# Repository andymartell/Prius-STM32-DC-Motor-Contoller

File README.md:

# Prius-STM32-DC-Motor-Contoller

18/10/20  Updated the following:

- corrected tracking error around MG1 and MG2 current sensors.  J7 footprint updated (J1 left unchanged as tracking layout is currently ok).
- updated file names to remove spaces
- removed SG3204 and TX4313 -5V charge pumps and added LM2776 in their place in line with Jack Bauers latest updates

17/10/20  Initial release of files for manufacture.  
There are issues with these files, so use at your own risk.  
An updated version will follow once initial testing is complete!

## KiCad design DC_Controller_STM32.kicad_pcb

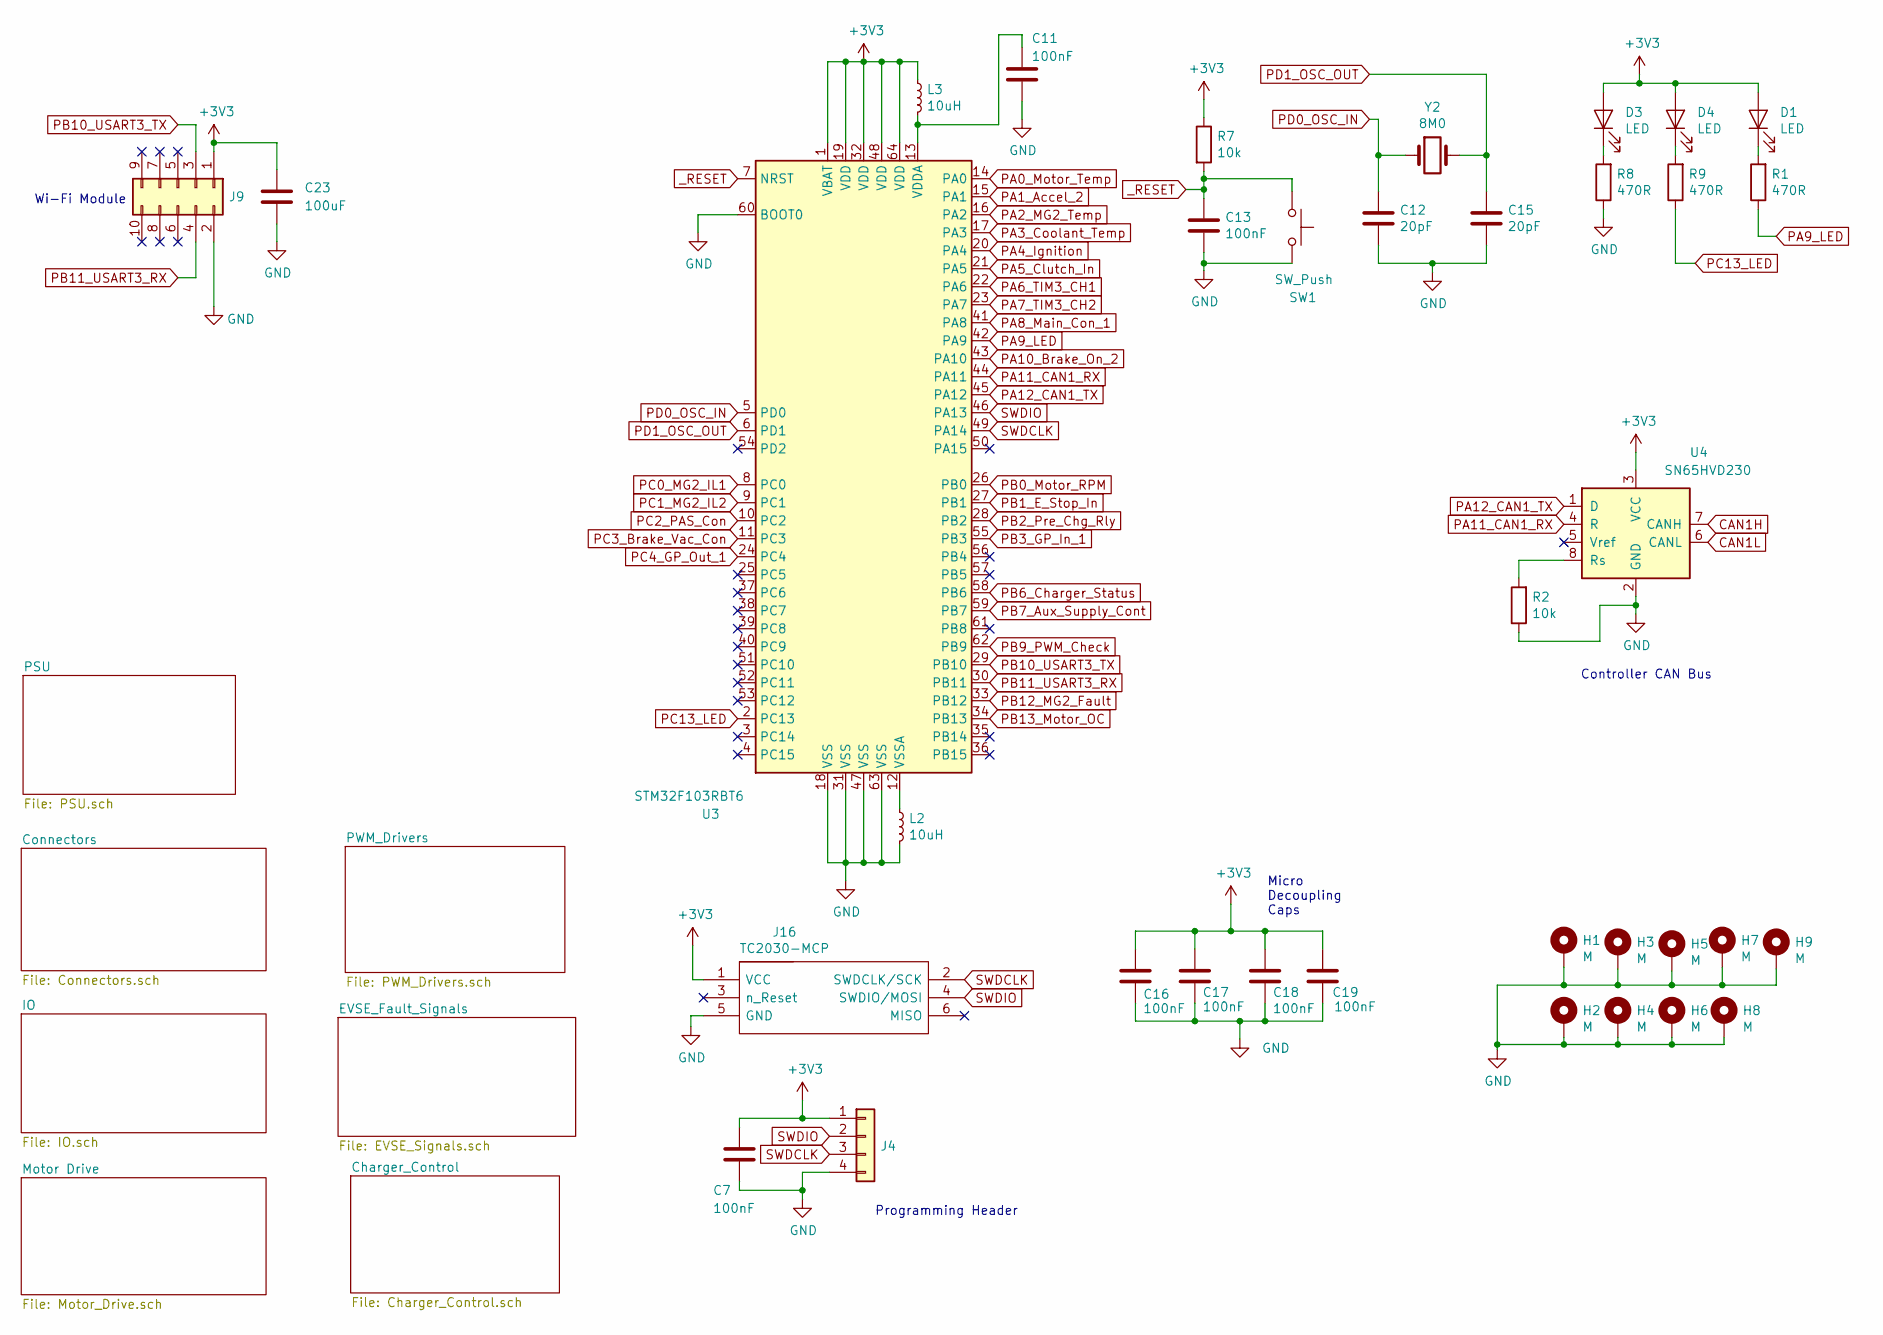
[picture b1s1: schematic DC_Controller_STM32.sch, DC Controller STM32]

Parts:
C7, C11, C13, C16, C17, C18, C19: 100nF; C_0603_1608Metric
C12, C15: 20pF; C_0603_1608Metric
C23: 100uF; CP_EIA-3528-21_Kemet-B
D1, D3, D4: LED; LED_0805_2012Metric
H1, H2, H3, H4, H5, H6, H7, H8, H9: M; MountingHole_3.2mm_M3_Pad
J4: Conn_01x04; PinHeader_1x04_P2.54mm_Vertical
J9: Conn_02x05_Odd_Even; PinHeader_2x05_P2.54mm_Horizontal
J16: TC2030-MCP; TC2030MCP; Manufacturer_Part_Number TC2030-MCP
L2, L3: 10uH; L_0805_2012Metric
R1, R8, R9: 470R; R_0603_1608Metric
R2, R7: 10k; R_0603_1608Metric
SW1: SW_Push; Panasonic_EVQPUK_EVQPUB
U3: STM32F103RBT6; LQFP-64_10x10mm_P0.5mm
U4: SN65HVD230; SOIC-8_3.9x4.9mm_P1.27mm
Y2: 8M0; Crystal_SMD_5032-2Pin_5.0x3.2mm

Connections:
+3V3: C7.1, C16.1, C17.1, C18.1, C19.1, C23.1, D1.2 (A), D3.2 (A), D4.2 (A), J4.1, J9.1, J16.1 (VCC), L3.1, R7.1, U3.1 (VBAT), U3.19 (VDD), U3.32 (VDD), U3.48 (VDD), U3.64 (VDD), U4.3 (VCC); also elsewhere on the board
CAN1H: U4.7 (CANH); also elsewhere on the board
CAN1L: U4.6 (CANL); also elsewhere on the board
GND: C7.2, C11.2, C12.2, C13.2, C15.2, C16.2, C17.2, C18.2, C19.2, C23.2, H1.1, H2.1, H3.1, H4.1, H5.1, H6.1, H7.1, H8.1, H9.1, J4.4, J9.2, J16.5 (GND), L2.2, R2.1, R8.1, SW1.2, U3.18 (VSS), U3.31 (VSS), U3.47 (VSS), U3.60 (BOOT0), U3.63 (VSS), U4.2 (GND); also elsewhere on the board
unnamed: C11.1, L3.2, U3.13 (VDDA)
unnamed: D1.1 (K), R1.2
unnamed: D3.1 (K), R8.2
unnamed: D4.1 (K), R9.2
unnamed: L2.1, U3.12 (VSSA)
unnamed: R2.2, U4.8 (Rs)
PA0_Motor_Temp: U3.14 (PA0); also elsewhere on the board
PA1_Accel_2: U3.15 (PA1); also elsewhere on the board
PA2_MG2_Temp: U3.16 (PA2); also elsewhere on the board
PA3_Coolant_Temp: U3.17 (PA3); also elsewhere on the board
PA4_Ignition: U3.20 (PA4); also elsewhere on the board
PA5_Clutch_In: U3.21 (PA5); also elsewhere on the board
PA6_TIM3_CH1: U3.22 (PA6); also elsewhere on the board
PA7_TIM3_CH2: U3.23 (PA7); also elsewhere on the board
PA8_Main_Con_1: U3.41 (PA8); also elsewhere on the board
PA9_LED: R1.1, U3.42 (PA9)
PA10_Brake_On_2: U3.43 (PA10); also elsewhere on the board
PA11_CAN1_RX: U3.44 (PA11), U4.4 (R)
PA12_CAN1_TX: U3.45 (PA12), U4.1 (D)
PB0_Motor_RPM: U3.26 (PB0); also elsewhere on the board
PB1_E_Stop_In: U3.27 (PB1); also elsewhere on the board
PB2_Pre_Chg_Rly: U3.28 (PB2); also elsewhere on the board
PB3_GP_In_1: U3.55 (PB3); also elsewhere on the board
PB6_Charger_Status: U3.58 (PB6); also elsewhere on the board
PB7_Aux_Supply_Cont: U3.59 (PB7); also elsewhere on the board
PB9_PWM_Check: U3.62 (PB9); also elsewhere on the board
PB10_USART3_TX: J9.3, U3.29 (PB10)
PB11_USART3_RX: J9.4, U3.30 (PB11)
PB12_MG2_Fault: U3.33 (PB12); also elsewhere on the board
PB13_Motor_OC: U3.34 (PB13); also elsewhere on the board
PC0_MG2_IL1: U3.8 (PC0); also elsewhere on the board
PC1_MG2_IL2: U3.9 (PC1); also elsewhere on the board
PC2_PAS_Con: U3.10 (PC2); also elsewhere on the board
PC3_Brake_Vac_Con: U3.11 (PC3); also elsewhere on the board
PC4_GP_Out_1: U3.24 (PC4); also elsewhere on the board
PC13_LED: R9.1, U3.2 (PC13)
PD0_OSC_IN: C12.1, U3.5 (PD0), Y2.1
PD1_OSC_OUT: C15.1, U3.6 (PD1), Y2.2
SWDCLK: J4.3, J16.2 (SWDCLK/SCK), U3.49 (PA14)
SWDIO: J4.2, J16.4 (SWDIO/MOSI), U3.46 (PA13)
_RESET: C13.1, R7.2, SW1.1, U3.7 (NRST)

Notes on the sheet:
Programming Header
Wi-Fi Module
Micro Decoupling Caps
Controller CAN Bus

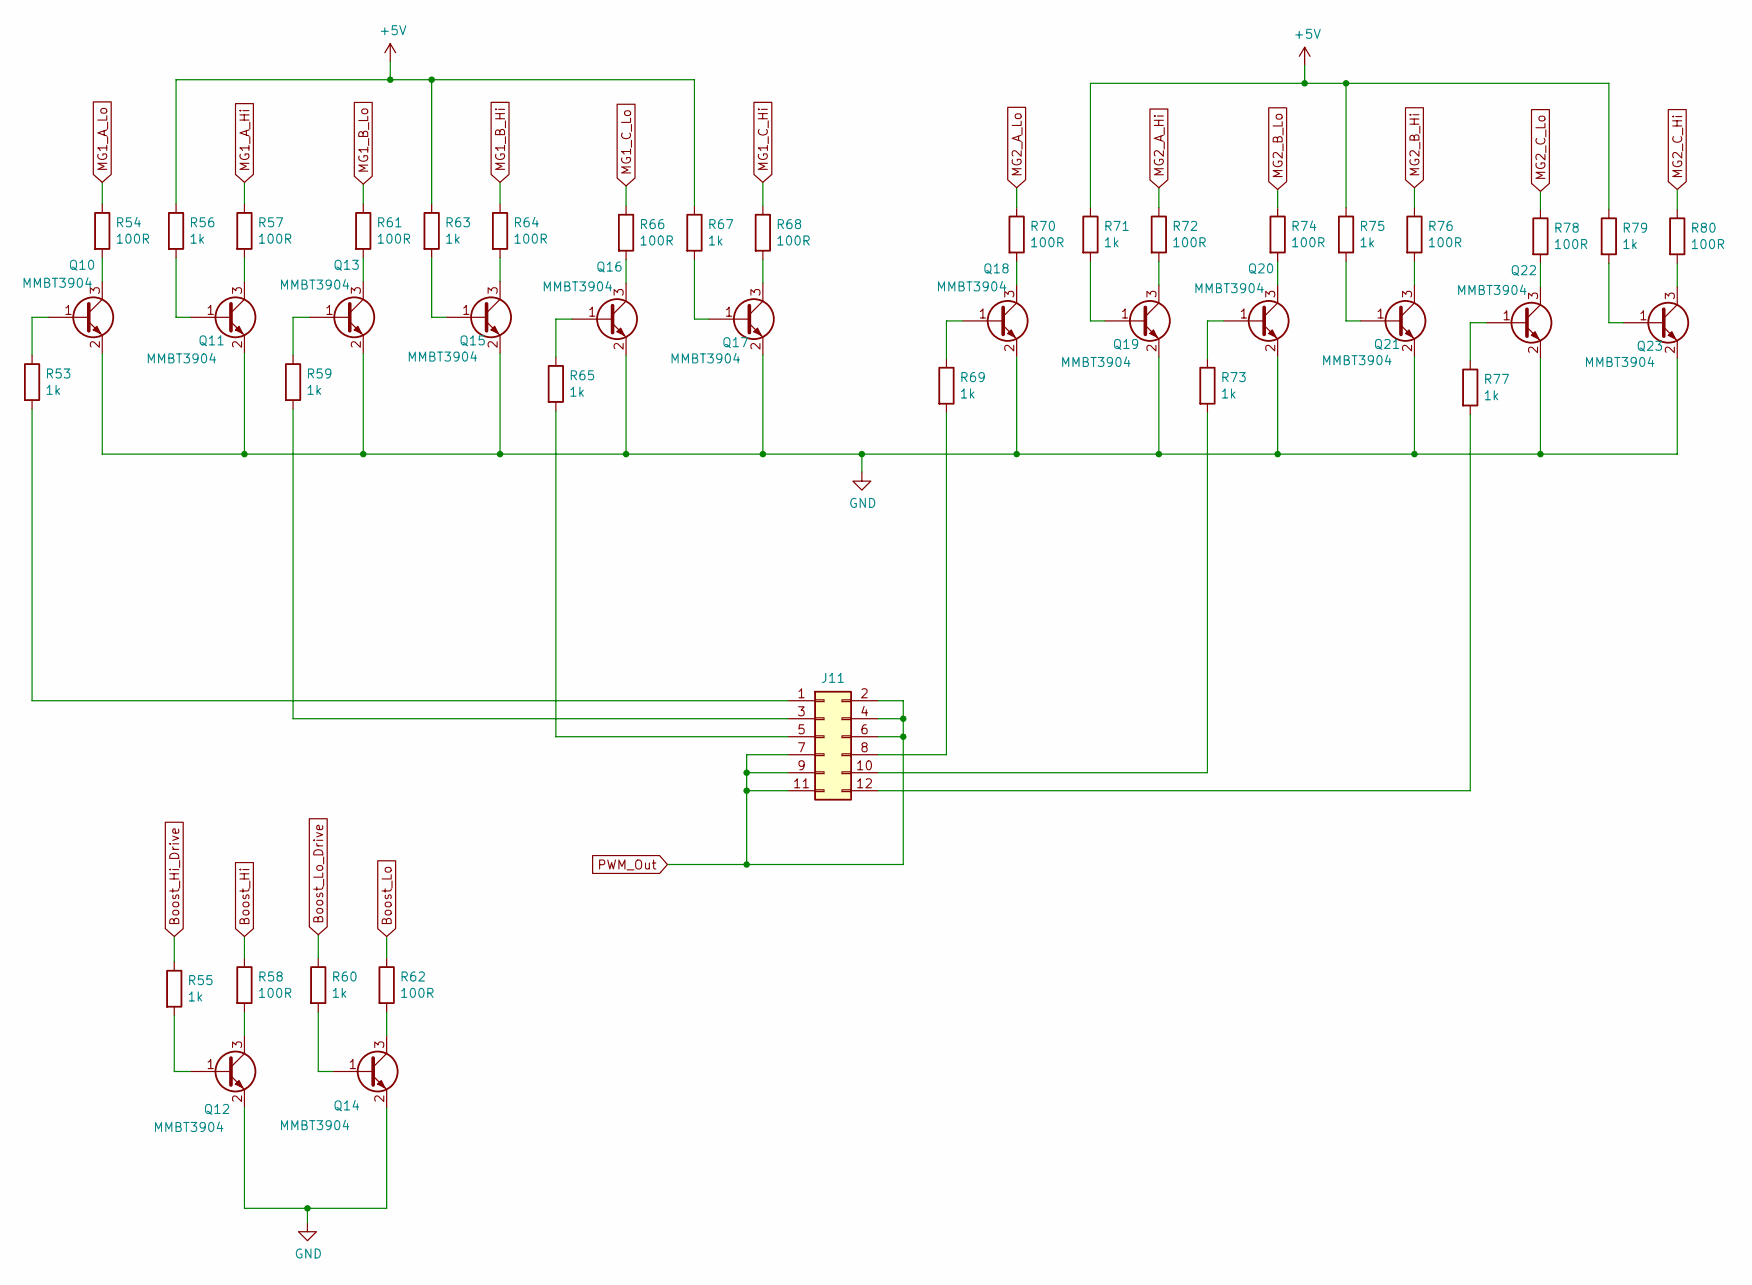
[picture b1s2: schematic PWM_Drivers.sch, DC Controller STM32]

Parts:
J11: Conn_02x06_Odd_Even; PinHeader_2x06_P2.54mm_Vertical
Q10, Q11, Q12, Q13, Q14, Q15, Q16, Q17, Q18, Q19, Q20, Q21, Q22, Q23: MMBT3904; SOT-23
R53, R55, R56, R59, R60, R63, R65, R67, R69, R71, R73, R75, R77, R79: 1k; R_0603_1608Metric
R54, R57, R58, R61, R62, R64, R66, R68, R70, R72, R74, R76, R78, R80: 100R; R_0603_1608Metric

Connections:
+5V: R56.1, R63.1, R67.1, R71.1, R75.1, R79.1; also elsewhere on the board
Boost_Hi: R58.1; also elsewhere on the board
Boost_Hi_Drive: R55.1; also elsewhere on the board
Boost_Lo: R62.1; also elsewhere on the board
Boost_Lo_Drive: R60.1; also elsewhere on the board
GND: Q10.2 (E), Q11.2 (E), Q12.2 (E), Q13.2 (E), Q14.2 (E), Q15.2 (E), Q16.2 (E), Q17.2 (E), Q18.2 (E), Q19.2 (E), Q20.2 (E), Q21.2 (E), Q22.2 (E), Q23.2 (E); also elsewhere on the board
MG1_A_Hi: R57.1; also elsewhere on the board
MG1_A_Lo: R54.1; also elsewhere on the board
MG1_B_Hi: R64.1; also elsewhere on the board
MG1_B_Lo: R61.1; also elsewhere on the board
MG1_C_Hi: R68.1; also elsewhere on the board
MG1_C_Lo: R66.1; also elsewhere on the board
MG2_A_Hi: R72.1; also elsewhere on the board
MG2_A_Lo: R70.1; also elsewhere on the board
MG2_B_Hi: R76.1; also elsewhere on the board
MG2_B_Lo: R74.1; also elsewhere on the board
MG2_C_Hi: R80.1; also elsewhere on the board
MG2_C_Lo: R78.1; also elsewhere on the board
unnamed: J11.1, R53.2
unnamed: J11.3, R59.2
unnamed: J11.5, R65.2
unnamed: J11.8, R69.2
unnamed: J11.10, R73.2
unnamed: J11.12, R77.2
unnamed: Q10.1 (B), R53.1
unnamed: Q10.3 (C), R54.2
unnamed: Q11.1 (B), R56.2
unnamed: Q11.3 (C), R57.2
unnamed: Q12.1 (B), R55.2
unnamed: Q12.3 (C), R58.2
unnamed: Q13.1 (B), R59.1
unnamed: Q13.3 (C), R61.2
unnamed: Q14.1 (B), R60.2
unnamed: Q14.3 (C), R62.2
unnamed: Q15.1 (B), R63.2
unnamed: Q15.3 (C), R64.2
unnamed: Q16.1 (B), R65.1
unnamed: Q16.3 (C), R66.2
unnamed: Q17.1 (B), R67.2
unnamed: Q17.3 (C), R68.2
unnamed: Q18.1 (B), R69.1
unnamed: Q18.3 (C), R70.2
unnamed: Q19.1 (B), R71.2
unnamed: Q19.3 (C), R72.2
unnamed: Q20.1 (B), R73.1
unnamed: Q20.3 (C), R74.2
unnamed: Q21.1 (B), R75.2
unnamed: Q21.3 (C), R76.2
unnamed: Q22.1 (B), R77.1
unnamed: Q22.3 (C), R78.2
unnamed: Q23.1 (B), R79.2
unnamed: Q23.3 (C), R80.2
PWM_Out: J11.2, J11.4, J11.6, J11.7, J11.9, J11.11; also elsewhere on the board

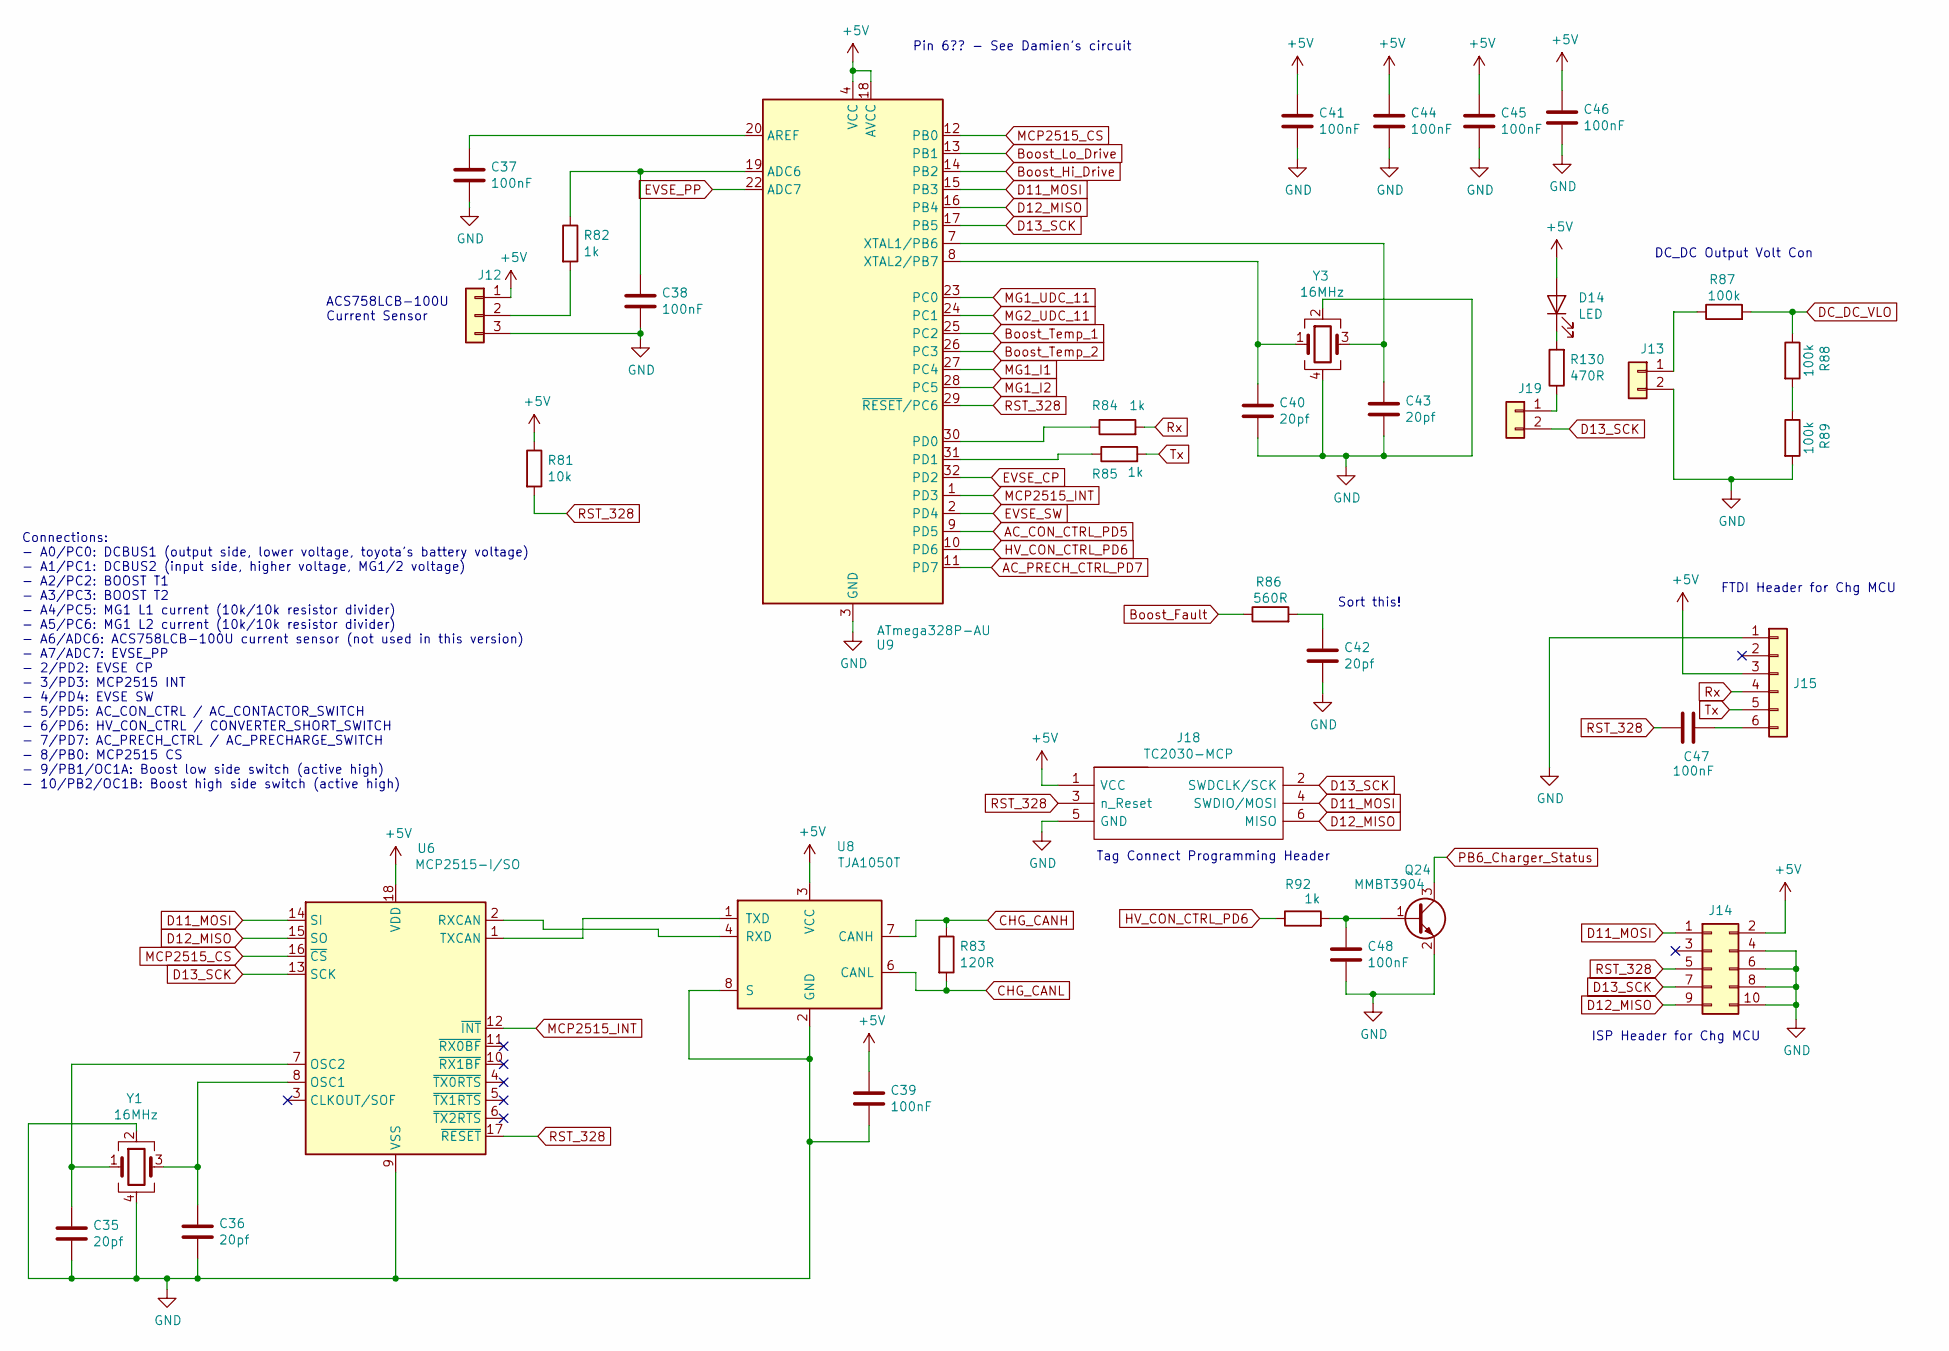
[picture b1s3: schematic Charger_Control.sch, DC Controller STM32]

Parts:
C35, C36, C40, C42, C43: 20pf; C_0603_1608Metric
C37, C38, C39, C41, C44, C45, C46, C47, C48: 100nF; C_0603_1608Metric
D14: LED; LED_0805_2012Metric
J12: Conn_01x03; PinHeader_1x03_P2.54mm_Vertical
J13, J19: Conn_01x02; PinHeader_1x02_P2.54mm_Vertical
J14: Conn_02x05_Odd_Even; PinHeader_2x05_P2.54mm_Vertical
J15: Conn_01x06; PinHeader_1x06_P2.54mm_Vertical
J18: TC2030-MCP; TC2030MCP; Manufacturer_Part_Number TC2030-MCP
Q24: MMBT3904; SOT-23
R81: 10k; R_0603_1608Metric
R82, R84, R85, R92: 1k; R_0603_1608Metric
R83: 120R; R_0603_1608Metric
R86: 560R; R_0603_1608Metric
R87, R88, R89: 100k; R_0603_1608Metric
R130: 470R; R_0603_1608Metric
U6: MCP2515-I/SO; SOIC-18W_7.5x11.6mm_P1.27mm
U8: TJA1050T; SOIC-8_3.9x4.9mm_P1.27mm
U9: ATmega328P-AU; TQFP-32_7x7mm_P0.8mm
Y1, Y3: 16MHz; Crystal_SMD_3225-4Pin_3.2x2.5mm

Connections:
+5V: C39.1, C41.1, C44.1, C45.1, C46.1, D14.2 (A), J12.1, J14.2, J15.3, J18.1 (VCC), R81.1, U6.18 (VDD), U8.3 (VCC), U9.4 (VCC), U9.6 (VCC), U9.18 (AVCC); also elsewhere on the board
AC_CON_CTRL_PD5: U9.9 (PD5); also elsewhere on the board
AC_PRECH_CTRL_PD7: U9.11 (PD7); also elsewhere on the board
Boost_Fault: R86.1; also elsewhere on the board
Boost_Hi_Drive: U9.14 (PB2); also elsewhere on the board
Boost_Lo_Drive: U9.13 (PB1); also elsewhere on the board
Boost_Temp_1: U9.25 (PC2); also elsewhere on the board
Boost_Temp_2: U9.26 (PC3); also elsewhere on the board
CHG_CANH: R83.1, U8.7 (CANH); also elsewhere on the board
CHG_CANL: R83.2, U8.6 (CANL); also elsewhere on the board
D11_MOSI: J14.1, J18.4 (SWDIO/MOSI), U6.14 (SI), U9.15 (PB3)
D12_MISO: J14.9, J18.6 (MISO), U6.15 (SO), U9.16 (PB4)
D13_SCK: J14.7, J18.2 (SWDCLK/SCK), J19.2, U6.13 (SCK), U9.17 (PB5)
DC_DC_VLO: R87.2, R88.1; also elsewhere on the board
EVSE_CP: U9.32 (PD2); also elsewhere on the board
EVSE_PP: U9.22 (ADC7); also elsewhere on the board
EVSE_SW: U9.2 (PD4); also elsewhere on the board
GND: C35.2, C36.2, C37.2, C38.2, C39.2, C40.2, C41.2, C42.2, C43.2, C44.2, C45.2, C46.2, C48.2, J12.3, J13.2, J14.4, J14.6, J14.8, J14.10, J15.1, J18.5 (GND), Q24.2 (E), R89.2, U6.9 (VSS), U8.2 (GND), U8.8 (S), U9.3 (GND), U9.5 (GND), U9.21 (GND), Y1.2, Y1.4, Y3.2, Y3.4; also elsewhere on the board
HV_CON_CTRL_PD6: R92.1, U9.10 (PD6); also elsewhere on the board
MCP2515_CS: U6.16 (~CS), U9.12 (PB0)
MCP2515_INT: U6.12 (~INT), U9.1 (PD3)
MG1_I1: U9.27 (PC4); also elsewhere on the board
MG1_I2: U9.28 (PC5); also elsewhere on the board
MG1_UDC_11: U9.23 (PC0); also elsewhere on the board
MG2_UDC_11: U9.24 (PC1); also elsewhere on the board
unnamed: C35.1, U6.7 (OSC2), Y1.1
unnamed: C36.1, U6.8 (OSC1), Y1.3
unnamed: C37.1, U9.20 (AREF)
unnamed: C38.1, R82.1, U9.19 (ADC6)
unnamed: C40.1, U9.8 (XTAL2/PB7), Y3.1
unnamed: C42.1, R86.2
unnamed: C43.1, U9.7 (XTAL1/PB6), Y3.3
unnamed: C47.1, J15.6
unnamed: C48.1, Q24.1 (B), R92.2
unnamed: D14.1 (K), R130.2
unnamed: J12.2, R82.2
unnamed: J13.1, R87.1
unnamed: J19.1, R130.1
unnamed: R84.1, U9.30 (PD0)
unnamed: R85.1, U9.31 (PD1)
unnamed: R88.2, R89.1
unnamed: U6.1 (TXCAN), U8.1 (TXD)
unnamed: U6.2 (RXCAN), U8.4 (RXD)
PB6_Charger_Status: Q24.3 (C); also elsewhere on the board
RST_328: C47.2, J14.5, J18.3 (n_Reset), R81.2, U6.17 (~RESET), U9.29 (~RESET~/PC6)
Rx: J15.4, R84.2
Tx: J15.5, R85.2

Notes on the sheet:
Pin 6?? - See Damien's circuit
ACS758LCB-100U Current Sensor
Sort this!
DC_DC Output Volt Con
FTDI Header for Chg MCU
ISP Header for Chg MCU
Connections: - A0/PC0: DCBUS1 (output side, lower voltage, toyota's battery voltage) - A1/PC1: DCBUS2 (input side, higher voltage, MG1/2 voltage) - A2/PC2: BOOST T1 - A3/PC3: BOOST T2 - A4/PC5: MG1 L1 current (10k/10k resistor divider) - A5/PC6: MG1 L2 current (10k/10k resistor divider) - A6/ADC6: 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
Tag Connect Programming Header

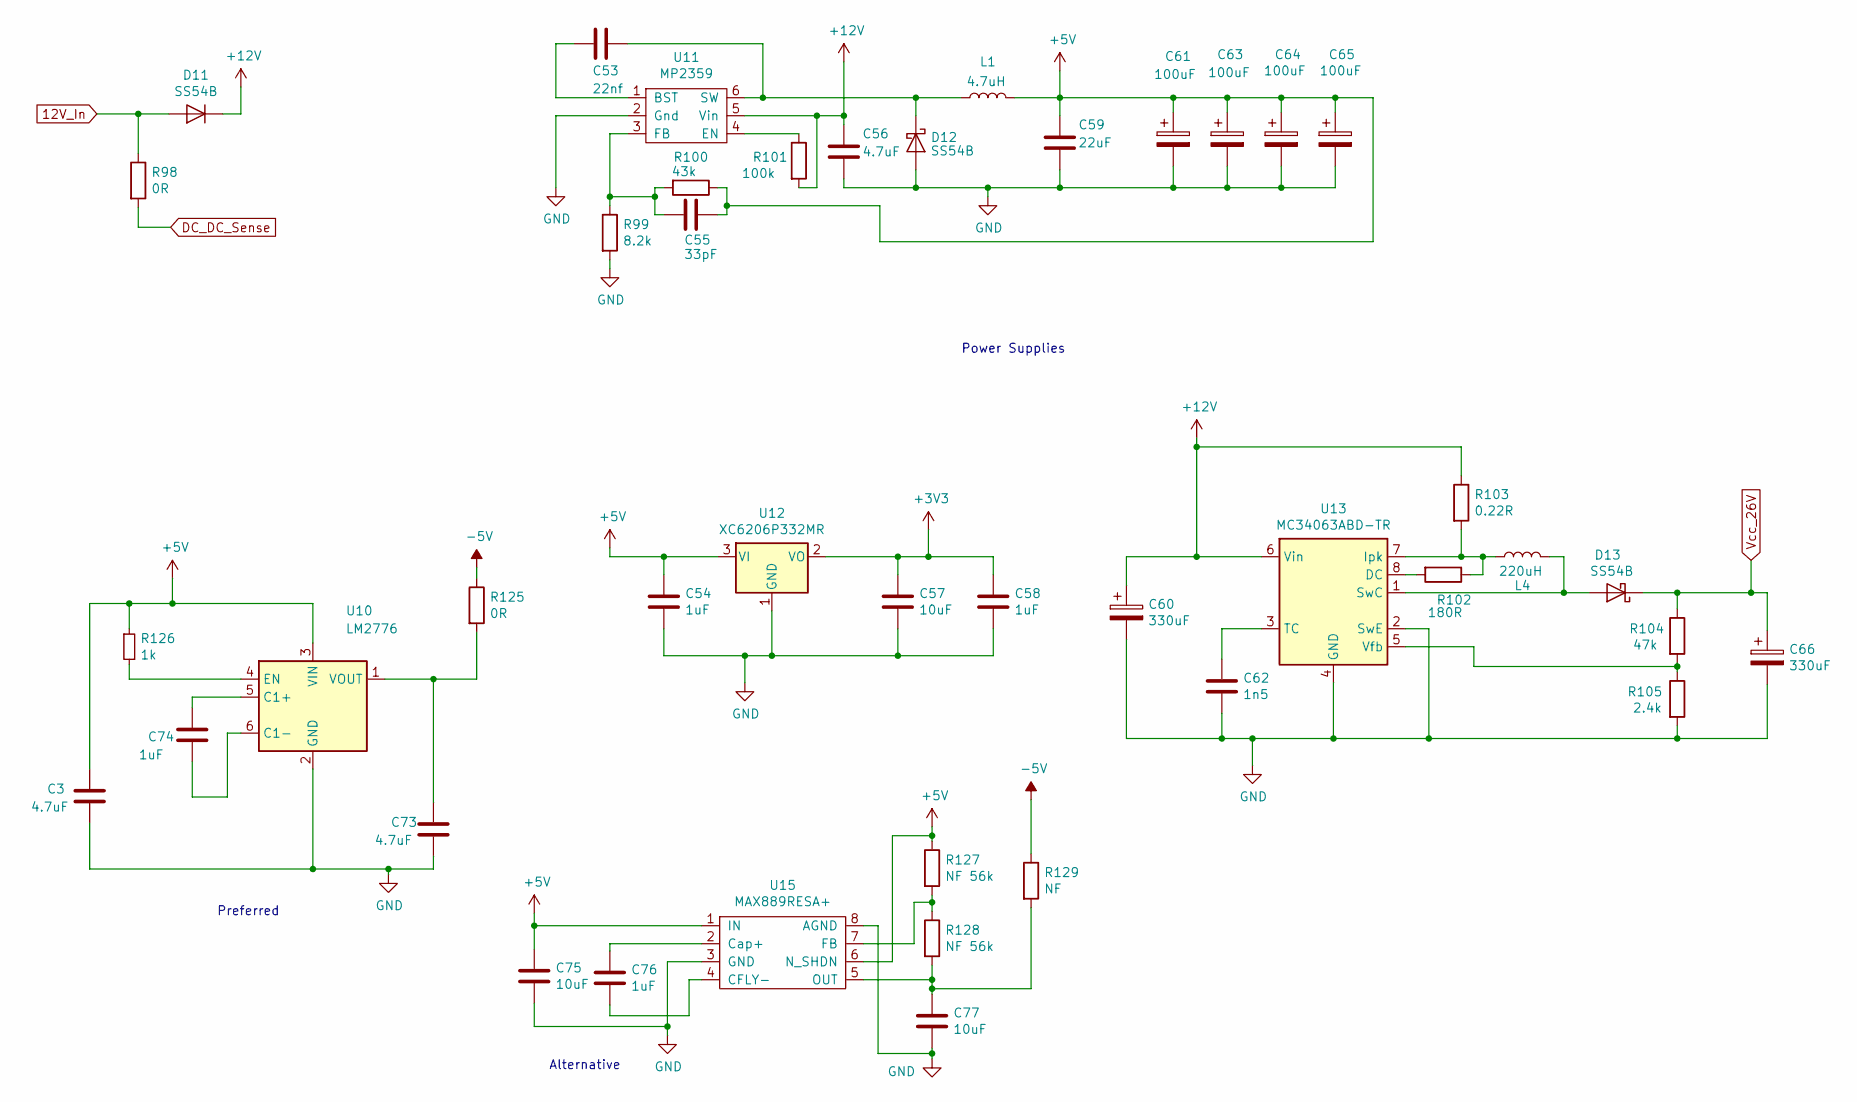
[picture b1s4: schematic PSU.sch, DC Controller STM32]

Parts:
C3, C56, C73: 4.7uF; C_0805_2012Metric
C53: 22nf; C_0603_1608Metric
C54, C58, C76: 1uF; C_0603_1608Metric
C55: 33pF; C_0603_1608Metric
C57, C75, C77: 10uF; C_0805_2012Metric
C59: 22uF; C_0805_2012Metric
C60, C66: 330uF; CP_Elec_10x10
C61, C63, C64, C65: 100uF; CP_EIA-3528-21_Kemet-B
C62: 1n5; C_0805_2012Metric
C74: 1uF; C_0805_2012Metric
D11, D12, D13: SS54B; D_SMA
L1: 4.7uH; L_1210_3225Metric
L4: 220uH; L_12x12mm_H6mm
R98, R125: 0R; R_0603_1608Metric
R99: 8.2k; R_0603_1608Metric
R100: 43k; R_0603_1608Metric
R101: 100k; R_0603_1608Metric
R102: 180R; R_0603_1608Metric
R103: 0.22R; R_0805_2012Metric
R104: 47k; R_0603_1608Metric
R105: 2.4k; R_0603_1608Metric
R126: 1k; R_0603_1608Metric
R127, R128: NF 56k; R_0603_1608Metric
R129: NF; R_0603_1608Metric
U10: LM2776; SOT-23-6
U11: MP2359; TSOT-23-6
U12: XC6206P332MR; SOT-23
U13: MC34063ABD-TR; SOIC-8_3.9x4.9mm_P1.27mm
U15: MAX889RESA+; SOIC-8_3.9x4.9mm_P1.27mm

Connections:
12V_In: D11.2 (A), R98.1; also elsewhere on the board
+3V3: C57.1, C58.1, U12.2 (VO); also elsewhere on the board
+5V: C3.1, C54.1, C55.1, C59.1, C61.1, C63.1, C64.1, C65.1, C75.1, L1.2, R100.1, R126.1, R127.1, U10.3 (VIN), U12.3 (VI), U15.1 (IN), U15.6 (N_SHDN); also elsewhere on the board
+12V: C56.1, C60.1, D11.1 (K), R101.2, R103.1, U11.5 (Vin), U13.6 (Vin); also elsewhere on the board
-5V: R125.1, R129.1; also elsewhere on the board
DC_DC_Sense: R98.2; also elsewhere on the board
GND: C3.2, C54.2, C56.2, C57.2, C58.2, C59.2, C60.2, C61.2, C62.2, C63.2, C64.2, C65.2, C66.2, C73.2, C75.2, C77.2, D12.2 (A), R99.2, R105.2, U10.2 (GND), U11.2 (Gnd), U12.1 (GND), U13.2 (SwE), U13.4 (GND), U15.3 (GND), U15.8 (AGND); also elsewhere on the board
unnamed: C53.1, D12.1 (K), L1.1, U11.6 (SW)
unnamed: C53.2, U11.1 (BST)
unnamed: C55.2, R99.1, R100.2, U11.3 (FB)
unnamed: C62.1, U13.3 (TC)
unnamed: C73.1, R125.2, U10.1 (VOUT)
unnamed: C74.1, U10.5 (C1+)
unnamed: C74.2, U10.6 (C1-)
unnamed: C76.1, U15.2 (Cap+)
unnamed: C76.2, U15.4 (CFLY-)
unnamed: C77.1, R128.2, R129.2, U15.5 (OUT)
unnamed: D13.2 (A), L4.2, U13.1 (SwC)
unnamed: L4.1, R102.1, R103.2, U13.7 (Ipk)
unnamed: R101.1, U11.4 (EN)
unnamed: R102.2, U13.8 (DC)
unnamed: R104.2, R105.1, U13.5 (Vfb)
unnamed: R126.2, U10.4 (EN)
unnamed: R127.2, R128.1, U15.7 (FB)
Vcc_26V: C66.1, D13.1 (K), R104.1; also elsewhere on the board

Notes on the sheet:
Power Supplies
Preferred
Alternative

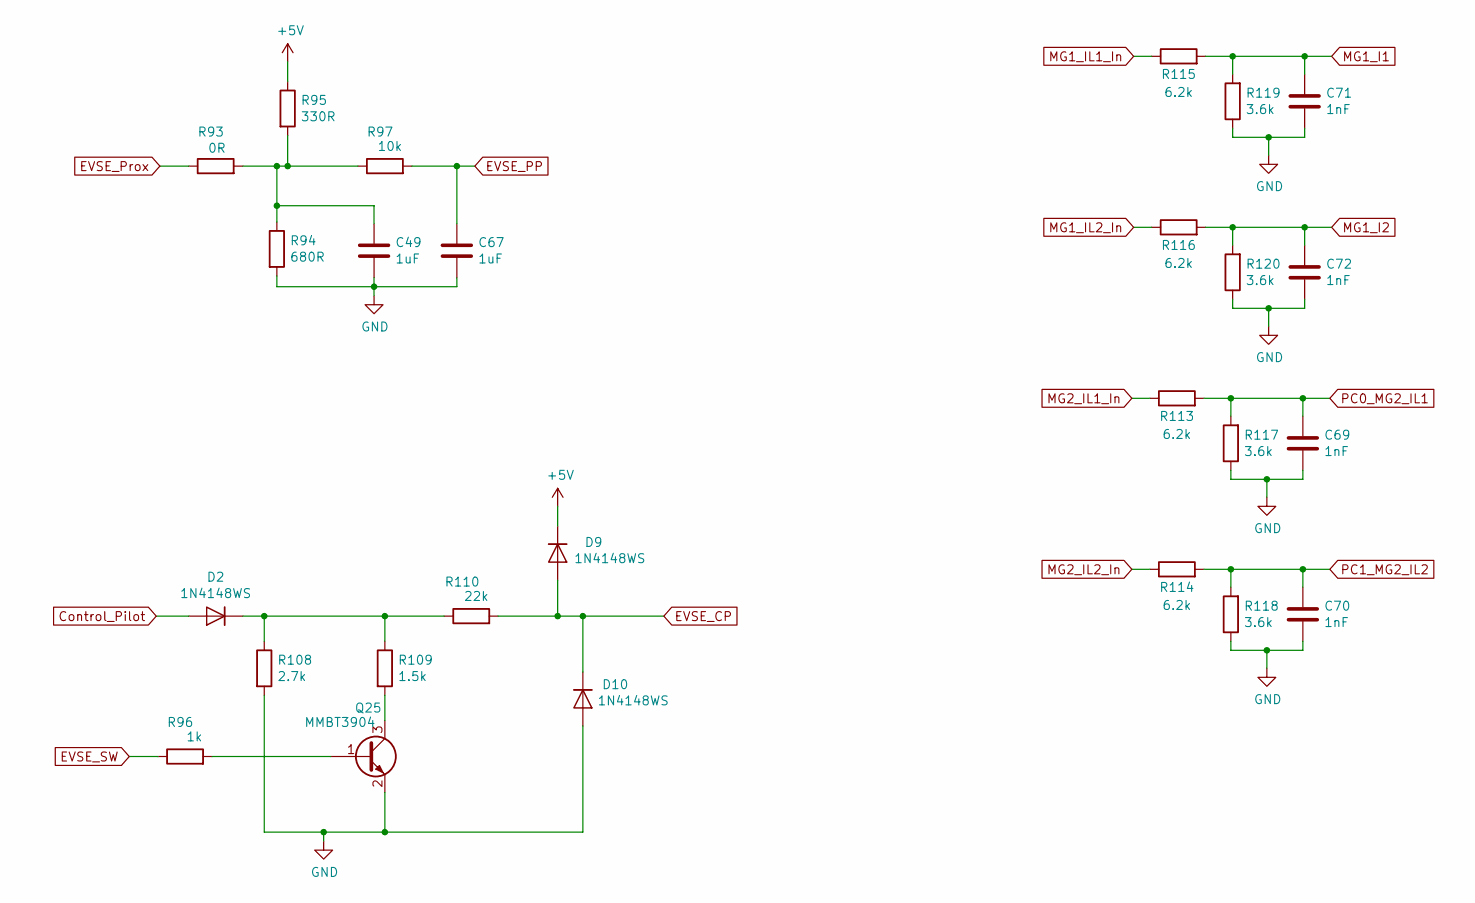
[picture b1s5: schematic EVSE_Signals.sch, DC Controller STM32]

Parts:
C49, C67: 1uF; C_0603_1608Metric
C69, C70, C71, C72: 1nF; C_0603_1608Metric
D2, D9, D10: 1N4148WS; D_SOD-323
Q25: MMBT3904; SOT-23
R93: 0R; R_0603_1608Metric
R94: 680R; R_0603_1608Metric
R95: 330R; R_0603_1608Metric
R96: 1k; R_0603_1608Metric
R97: 10k; R_0603_1608Metric
R108: 2.7k; R_0603_1608Metric
R109: 1.5k; R_0603_1608Metric
R110: 22k; R_0603_1608Metric
R113, R114, R115, R116: 6.2k; R_0603_1608Metric
R117, R118, R119, R120: 3.6k; R_0603_1608Metric

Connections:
+5V: D9.1 (K), R95.1; also elsewhere on the board
Control_Pilot: D2.2 (A); also elsewhere on the board
EVSE_CP: D9.2 (A), D10.1 (K), R110.2; also elsewhere on the board
EVSE_PP: C67.1, R97.2; also elsewhere on the board
EVSE_Prox: R93.1; also elsewhere on the board
EVSE_SW: R96.1; also elsewhere on the board
GND: C49.2, C67.2, C69.2, C70.2, C71.2, C72.2, D10.2 (A), Q25.2 (E), R94.2, R108.2, R117.1, R118.1, R119.1, R120.1; also elsewhere on the board
MG1_I1: C71.1, R115.2, R119.2; also elsewhere on the board
MG1_I2: C72.1, R116.2, R120.2; also elsewhere on the board
MG1_IL1_In: R115.1; also elsewhere on the board
MG1_IL2_In: R116.1; also elsewhere on the board
MG2_IL1_In: R113.1; also elsewhere on the board
MG2_IL2_In: R114.1; also elsewhere on the board
unnamed: C49.1, R93.2, R94.1, R95.2, R97.1
unnamed: D2.1 (K), R108.1, R109.1, R110.1
unnamed: Q25.1 (B), R96.2
unnamed: Q25.3 (C), R109.2
PC0_MG2_IL1: C69.1, R113.2, R117.2; also elsewhere on the board
PC1_MG2_IL2: C70.1, R114.2, R118.2; also elsewhere on the board
